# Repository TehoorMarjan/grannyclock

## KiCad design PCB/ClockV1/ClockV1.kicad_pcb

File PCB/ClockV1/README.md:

# GrannyClock PCB (v1.0)

## Overview

The GrannyClock PCB is an add-on module designed for the TFA Dostmann 60.3518.01 radio-controlled clock mechanism. It provides enhanced audio capabilities to create a talking/chiming clock while preserving battery life and the original clock functionality.

This PCB interfaces with the TFA clock module signal pins (MU, BR, BA, RF) to detect the current time and play appropriate audio files from an SD card through an integrated DFPlayer Mini MP3 module.

## Specifications

- **Dimensions**: 50x30mm, 2mm rounded corners, 2mm⌀ mounting holes
- **Power Supply**: 2xAA batteries with MT3608 step-up converter (2.0-3.0V to 3.3V)
- **Microcontroller**: ATtiny1616 (VQFN-20 package)
- **Audio**: DFPlayer Mini module with speaker outputs
- **Logic Level Translation**: MAX14611ETD+ bidirectional level shifter (1.5V ↔ 3.3V)
- **Interfaces**:
  - UPDI programming interface
  - Speaker connector
  - Clock module interface connector
  - Test points for debugging

👉 [Schematics](output/schematics/ClockV1.pdf)

## Key Features

- **Power Efficient Design**:

  - Step-up from 2×AA batteries
  - Power switching for the DFPlayer Mini
  - Low-power ATtiny1616
  - Low-power MAX14611 level shifter

- **Intelligent Operation**:

  - Monitors clock signals to determine the current time
  - Plays appropriate audio based on hour information (BCD encoded on MU line)
  - Light sensor for night-time muting

- **Debugging**:
  - Red and green LEDs
  - 7 testing points

## PCB Design Files

This repository contains all necessary KiCad files for the GrannyClock PCB:

- `ClockV1.kicad_sch` - Schematic capture file
- `ClockV1.kicad_pcb` - PCB layout file
- `ClockV1.kicad_pro` - KiCad project file
- `output/` - Generated output files (3D renders, PDFs)
- `production/` - Manufacturing files (gerbers, BOM, position files)

## Design Considerations

### Level Translation

The TFA clock module operates at 1.5V logic levels (single AA power cell), while the microcontroller uses 3.3V. A MAX14611ETD+ level translator chip provides reliable communication between these voltage domains. This component was chosen after testing revealed that traditional MOSFET-based level shifters were unreliable at 1.5V.

### Audio Playback Solution

The DFPlayer Mini module was selected for audio playback capabilities due to:

- Integrated MP3 decoder and amplifier
- Simple serial interface
- SD card file management
- Proven reliability

Power to this module is completely cut when not in use to maximize battery life, as it only needs to be active approximately 16 times per day for brief periods.

### Light Sensing

An onboard photoresistor allows the clock to detect ambient light levels and mute audio output during nighttime or in dark rooms, preventing disturbances during sleep.

## Manufacturing

The PCB is designed for manufacture through JLCPCB with SMT assembly. Key production files are located in the `production/` directory:

- `bom.csv` - Bill of Materials
- `positions.csv` - Component placement data
- `GrannyClock_1.0.zip` - Complete manufacturing package

Notes on component sourcing:

- The DFPlayer Mini module is not SMT assembled and must be manually soldered
- The photoresistor (LDR) needs manual installation
- The MAX14611ETD+ level shifter may require special sourcing if not available in the standard JLCPCB parts library

## Programming

The ATtiny1616 is programmed via the UPDI interface. Compatible programmers include:

- Microchip MPLAB Snap
- PICkit 4
- Any UPDI-compatible programmer
- Simple USB-TTL UART interface

## Integration with TFA Clock

This PCB interfaces with the TFA Dostmann 60.3518.01 clock module via a dedicated connector (J3), which connects to the following signal lines:

- **MU**: BCD-encoded hour value triggered at each hour
- **BA**: "Bell Activate" signal triggered at each hour
- **BR**: Reset signal sent during time adjustments
- **RF**: Demodulated DCF77 time signal
- **PON**: Signal indicating clock module is operational
- **GND**: Common ground

## Related Project Components

The GrannyClock is part of a larger project that includes:

- **Sniffer**: ESP32-based signal analysis tool used to reverse-engineer the TFA clock module
- **Firmware**: ATtiny1616 firmware (coming soon)
- **CAD**: 3D-printed case designs (coming soon)
- **Audio Files**: MP3 samples for the hourly announcements

## License

This hardware design is licensed under the [CERN Open Hardware License v2 - Permissive (CERN-OHL-P)](LICENSE).

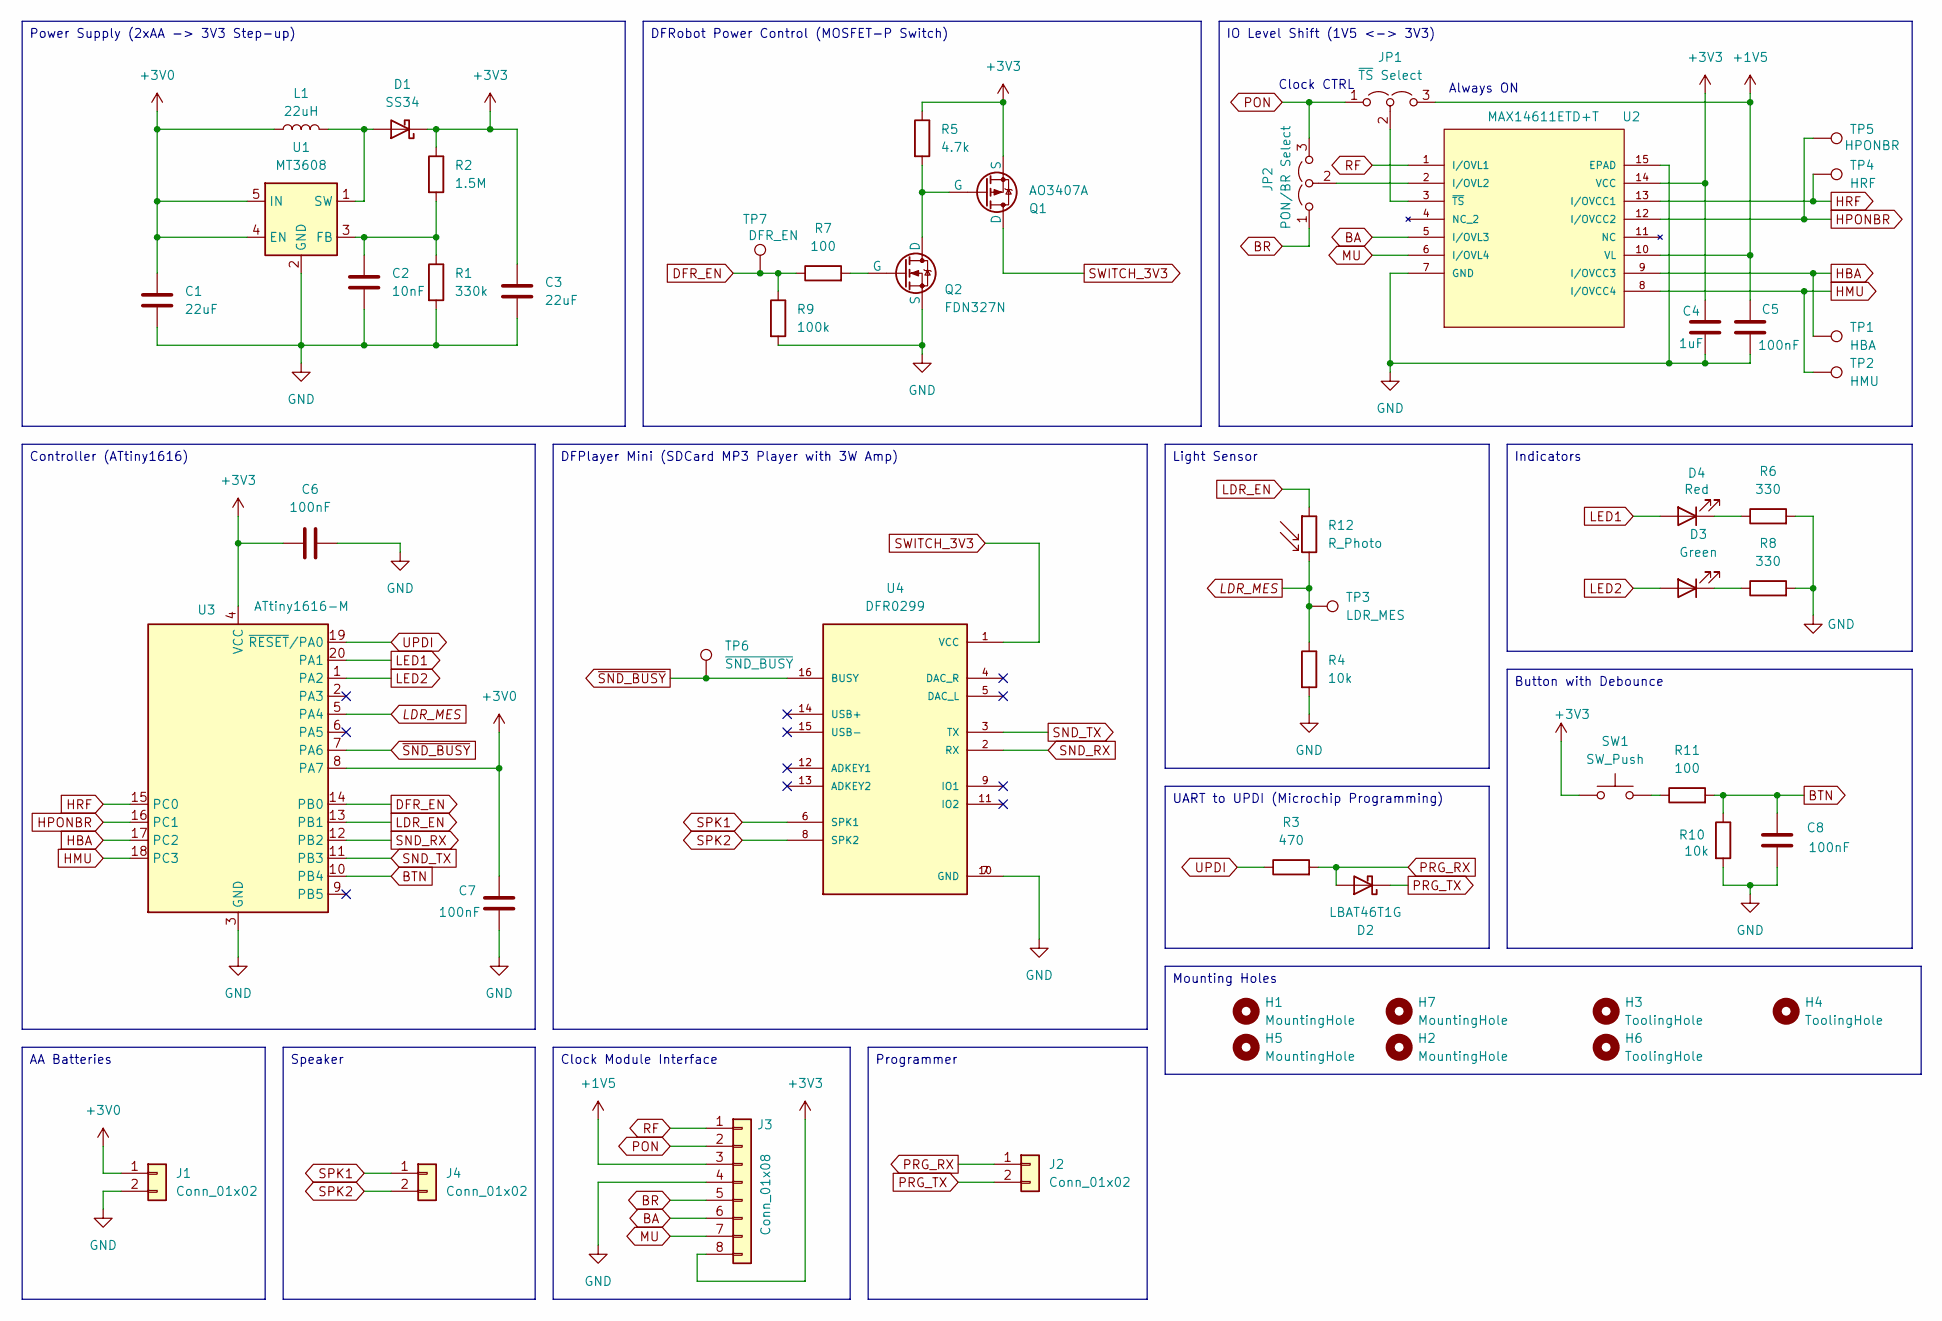
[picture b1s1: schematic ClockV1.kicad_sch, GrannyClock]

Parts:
C1, C3: 22uF; C_0603_1608Metric
C2: 10nF; C_0603_1608Metric
C4: 1uF; C_0603_1608Metric
C5, C6, C7, C8: 100nF; C_0603_1608Metric
D1: SS34; SS34_DIO_SS34
D2: LBAT46T1G; D_SOD-123
D3: Green; LED_0603_1608Metric
D4: Red; LED_0603_1608Metric
H1, H2, H5, H7: MountingHole; MountingHole_2mm
H3, H4, H6: ToolingHole; ToolingHole_1.152mm
J1, J2, J4: Conn_01x02; PinHeader_1x02_P2.54mm_Vertical
J3: Conn_01x08; PinHeader_1x08_P2.54mm_Vertical
JP1: ~{TS} Select; SolderJumper-3_P1.3mm_Open_RoundedPad1.0x1.5mm
JP2: PON/BR Select; SolderJumper-3_P1.3mm_Open_RoundedPad1.0x1.5mm
L1: 22uH; L_12x12mm_H4.5mm; MANUFACTURER_PART_NUMBER SDRH.1209CT.NLF220MT00; JLCPCB Part # C5123081
Q1: AO3407A; SOT-23-3; Manufacturer_Part_Number AO3407A; JLCPCB Part # C5224209
Q2: FDN327N; FDN327N_SSOT-3
R1: 330k; R_0603_1608Metric
R2: 1.5M; R_0603_1608Metric
R3: 470; R_0603_1608Metric
R4, R10: 10k; R_0603_1608Metric
R5: 4.7k; R_0603_1608Metric
R6, R8: 330; R_0603_1608Metric
R7, R11: 100; R_0603_1608Metric
R9: 100k; R_0603_1608Metric
R12: R_Photo; R_LDR_4.9x4.2mm_P2.54mm_Vertical
SW1: SW_Push; SW_PUSH_1P1T_6x3.5mm_H4.3_APEM_MJTP1243
TP1: HBA; TestPoint_Pad_D1.5mm
TP2: HMU; TestPoint_Pad_D1.5mm
TP3: LDR_MES; TestPoint_Pad_D1.5mm
TP4: HRF; TestPoint_Pad_D1.5mm
TP5: HPONBR; TestPoint_Pad_D1.5mm
TP6: ~{SND_BUSY}; TestPoint_Pad_D1.5mm
TP7: DFR_EN; TestPoint_Pad_D1.5mm
U1: MT3608; SOT-23-6
U2: MAX14611ETD+T; TDFN-14-1EP_3x3mm_P0.4mm_EP1.78x2.35mm; MANUFACTURER_PART_NUMBER MAX14611ETD+; JLCPCB Part # C2677488
U3: ATtiny1616-M; VQFN-20-1EP_3x3mm_P0.4mm_EP1.7x1.7mm_ThermalVias
U4: DFR0299; DFR0299_MODULE_DFR0299

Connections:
+1V5: C5.1, J3.3, JP1.3 (B), U2.10 (VL)
+3V0: C1.1, C7.2, J1.1, L1.1, U1.4 (EN), U1.5 (IN), U3.8 (PA7)
+3V3: C3.1, C4.1, C6.1, D1.1 (K), J3.8, Q1.3 (S), R2.1, R5.1, SW1.1, U2.14 (VCC), U3.4 (VCC)
BA: J3.6, U2.5 (I/OVL3)
BR: J3.5, JP2.1 (A)
BTN: C8.1, R10.1, R11.2, U3.10 (PB4)
DFR_EN: R7.1, R9.1, TP7.1, U3.14 (PB0)
GND: C1.2, C2.2, C3.2, C4.2, C5.2, C6.2, C7.1, C8.2, J1.2, J3.4, Q2.3 (S), R1.2, R4.2, R6.2, R8.2, R9.2, R10.2, U1.2 (GND), U2.7 (GND), U2.15 (EPAD), U3.3 (GND), U3.21 (GND), U4.7 (GND), U4.10 (GND)
HBA: TP1.1, U2.9 (I/OVCC3), U3.17 (PC2)
HMU: TP2.1, U2.8 (I/OVCC4), U3.18 (PC3)
HPONBR: TP5.1, U2.12 (I/OVCC2), U3.16 (PC1)
HRF: TP4.1, U2.13 (I/OVCC1), U3.15 (PC0)
LDR_EN: R12.1, U3.13 (PB1)
LDR_MES: R4.1, R12.2, TP3.1, U3.5 (PA4)
LED1: D4.2 (A), U3.20 (PA1)
LED2: D3.2 (A), U3.1 (PA2)
MU: J3.7, U2.6 (I/OVL4)
unnamed: D1.2 (A), L1.2, U1.1 (SW)
unnamed: D3.1 (K), R8.1
unnamed: D4.1 (K), R6.1
unnamed: JP1.2 (C), U2.3 (~TS)
unnamed: JP2.2 (C), U2.2 (I/OVL2)
unnamed: Q1.2 (G), Q2.1 (D), R5.2
unnamed: Q2.2 (G), R7.2
unnamed: R11.1, SW1.2
unnamed: C2.1, R1.1, R2.2, U1.3 (FB)
PON: J3.2, JP1.1 (A), JP2.3 (B)
PRG_RX: D2.2 (A), J2.1, R3.2
PRG_TX: D2.1 (K), J2.2
RF: J3.1, U2.1 (I/OVL1)
SND_RX: U3.12 (PB2), U4.2 (RX)
SND_TX: U3.11 (PB3), U4.3 (TX)
SPK1: J4.1, U4.6 (SPK1)
SPK2: J4.2, U4.8 (SPK2)
SWITCH_3V3: Q1.1 (D), U4.1 (VCC)
UPDI: R3.1, U3.19 (~RESET/PA0)
~SND_BUSY: TP6.1, U3.7 (PA6), U4.16 (BUSY)

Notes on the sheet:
Clock CTRL
Always ON
DFRobot Power Control (MOSFET-P Switch)
Indicators
Clock Module Interface
Button with Debounce
Speaker
Mounting Holes
AA Batteries
Controller (ATtiny1616)
DFPlayer Mini (SDCard MP3 Player with 3W Amp)
IO Level Shift (1V5 <-> 3V3)
UART to UPDI (Microchip Programming)
Power Supply (2xAA -> 3V3 Step-up)
Light Sensor
Programmer

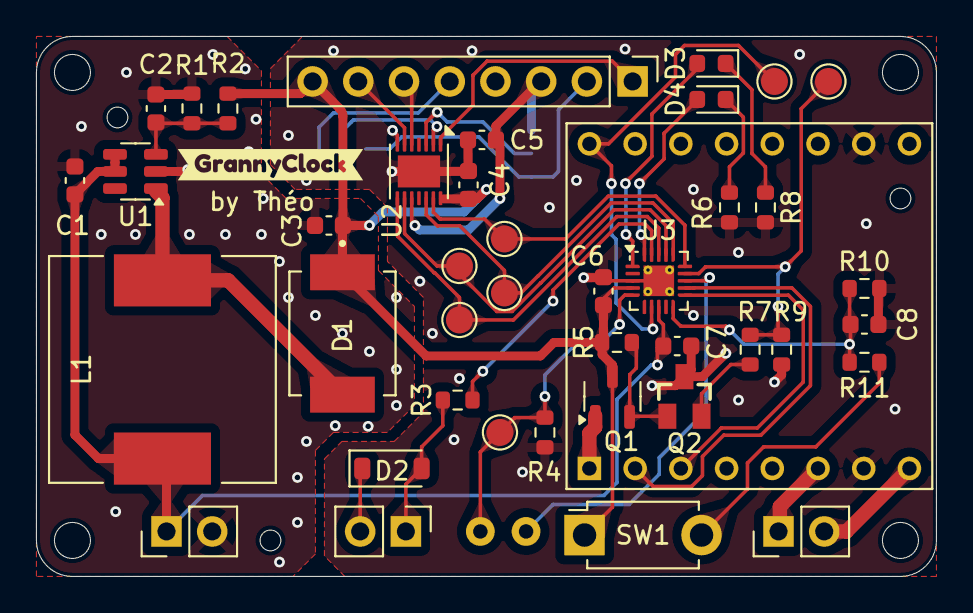
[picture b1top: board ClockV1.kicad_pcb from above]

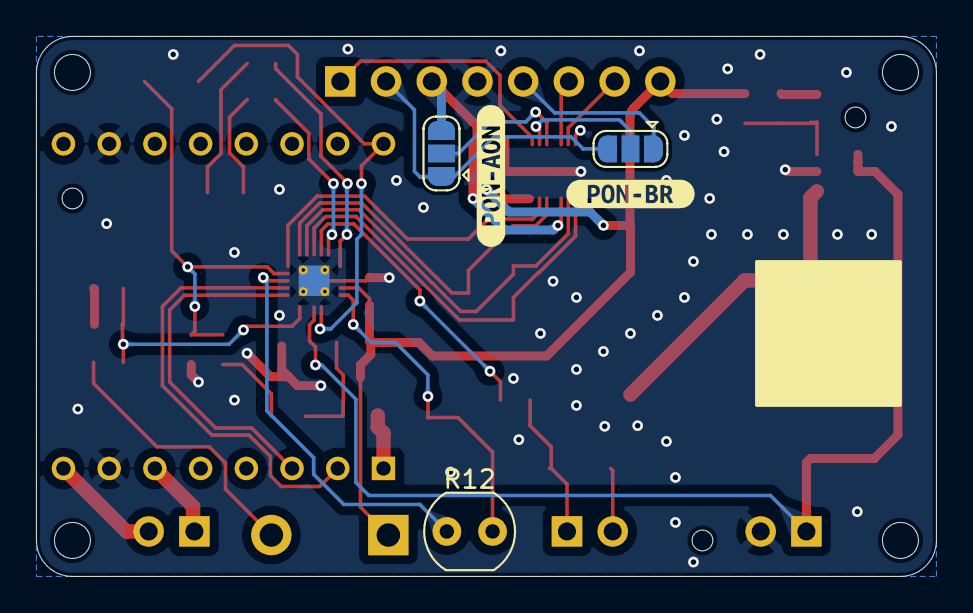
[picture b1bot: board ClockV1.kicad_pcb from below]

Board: 2 copper layers, 50.0 x 30.0 mm, 55 parts (5 on the bottom side), 37 nets.

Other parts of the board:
kibuzzard-1: G***; kibuzzard-681BEBFE
kibuzzard-2: G***; kibuzzard-681FCEAB
kibuzzard-3: G***; kibuzzard-681FCE61

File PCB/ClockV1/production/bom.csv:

Designator,Footprint,Quantity,Value,LCSC Part #
"C1, C3",0603,2,22uF,
C2,0603,1,10nF,
C4,0603,1,1uF,
"C5, C6, C7, C8",0603,4,100nF,
D1,SS34_DIO_SS34,1,SS34,
D2,D_SOD-123,1,LBAT46T1G,
L1,L_12x12mm_H4.5mm,1,22uH,C5123081
Q1,SOT-23-3,1,AO3407A,C5224209
Q2,FDN327N_SSOT-3,1,FDN327N,
R1,0603,1,330k,
"R10, R4",0603,2,10k,
"R11, R7",0603,2,100,
R2,0603,1,1.5M,
R3,0603,1,470,
R5,0603,1,4.7k,
"R6, R8",0603,2,330,
R9,0603,1,100k,
SW1,SW_PUSH_1P1T_6x3.5mm_H4.3_APEM_MJTP1243,1,SW_Push,
U1,SOT-23-6,1,MT3608,
U2,TDFN-14-1EP_3x3mm_P0.4mm_EP1.78x2.35mm,1,MAX14611ETD+T,C2677488
U3,VQFN-20-1EP_3x3mm_P0.4mm_EP1.7x1.7mm_ThermalVias,1,ATtiny1616-M,

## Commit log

2025-04-27 Add core functionality for signal logging and SD card management
    - Implemented RingBuffer class for event storage with thread safety.
    - Created SDCardManager class to handle SD card initialization and event saving.
    - Developed SignalLogger class to log RF signals and manage interrupts.
    - Added StatusIndicator class for visual feedback on system status.
    - Integrated all components in main application loop for signal monitoring and data saving.
    - Introduced CSV to VCD conversion script for data analysis.
2025-04-27 Fix image path for breadboard schematics in SPECS.md
2025-04-28 Add LICENSE and update README and SPECS for signal connections; fix analysis documentation
2025-05-07 PCB Version 1
2025-05-09 Production to JLCPCB
2025-05-10 Add LICENSE file and update README with project overview, specifications, features, and manufacturing details
2025-05-10 Add decoupling capacitors and signal selection jumper for MAX14611
    - Added decoupling capacitors (C5/100nF and C6/1uF) for the MAX14611 dual power supplies
    - Added solder jumper to allow selection between PON and BR signals for microcontroller input
    - Renamed net HBR to Net-(JP2-C) to better reflect its function as jumper connection
    - Added new HPONBR signal net for level shifter power control
    - Updated PCB date to 2025-05-11
2025-05-12 Update of PCB ClockV1
    - Export Silkscreen in 3D
    - Add jumper to select monitoring PON
    - Re-order references
    - Monitor +3V0 from uC with ADC and a decoupling capactior
    - Changed photoresistor footprint (actual part is smaller than expected)
2025-05-12 CAD: First try for a box
2025-05-14 Add switch to PCB
    - Added a single push button switch
    - Added RC filter for (pre-)debounce
    - Moved tooling hole to place the button
    - Removed some silkscreen labels to make room
    - Renumbered components depengind on their placement on the PCB
2025-05-15 Corrected debouncer
    - Capacitor was not positionned properly
2025-05-19 TFA Dostmann Clock Module (60.3518.01) 3D Model
2025-05-19 Add Dual AA Battery Holder modified CAD
2025-05-19 Replace BR signal with PON, remove RF timing restrictions, and update hardware design
    This commit makes significant changes to the Clock Sniffer project:
    1. Replaced BR (BR signal) with PON (Power ON signal):
    - Updated pin definitions in Config.h
    - Modified signal type enums and string mappings
    - Updated interrupt handlers and signal processing code
    - Adapted csv2vcd.py to use PON in the WIRES list
2025-05-23 Add HD-1688 clock mechanism model and documentation
    Adds complete modeling of the Sheng Bang HD-1688MRC inner clock mechanism with:
    - 3D model files (FCStd, STEP)
    - Dimensional reference (CSV)
    - Visual preview (PNG)
    - Comprehensive README with project context and copyright disclaimer
    - CC BY-NC-SA license
2025-05-23 Enhance csv2vcd.py to handle timestamp resets
    - Added timestamp reset detection (ESP32 reboots or overflows)
    - Automatically splits output into multiple VCD files when resets occur
    - Uses sequential naming convention: output.vcd, output_1.vcd, etc.
    - Updated README with usage information for this feature
2025-05-25 Moved Sniffer to Testing/Sniffer
2025-05-25 Store last changes in ClockV1 before deprecating
2025-05-26 Add DRV8833 solenoid driver test project
    This commit adds a complete test project for driving clock solenoids using the DRV8833 motor driver:
    Hardware components:
    - DRV8833 dual H-bridge motor driver (used for solenoid control)
    - ESP32 microcontroller
    - Clock solenoids (seconds and minutes hands)
    - 470 ohm resistors for current limiting
2025-05-27 Add ATtiny1616Boilerplate project with UPDI programming
    This commit introduces a complete boilerplate project for ATtiny1616 development:
    - Source code: Simple LED blink example on pin PA1
    - PlatformIO configuration: Setup for atmelmegaavr platform with UPDI programming
    - Circuit diagrams: Schematic and breadboard layouts showing proper UPDI connections
    - Auto-dependency installation: Script for automatic pymcuprog installation
    - Comprehensive documentation: Detailed README with hardware setup and programming guidelines
2025-05-27 Add README.md for GrannyClock testing projects overview and documentation
2025-05-27 PyGrannyTool provides several commands for testing different GrannyClock components.
    - Test a NEO-6M GPS module connection and monitor timestamp information
